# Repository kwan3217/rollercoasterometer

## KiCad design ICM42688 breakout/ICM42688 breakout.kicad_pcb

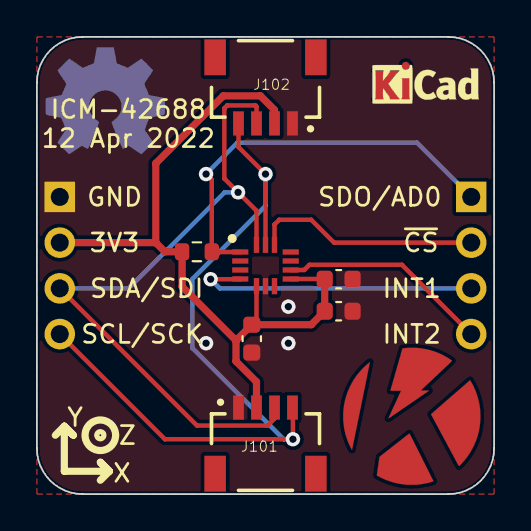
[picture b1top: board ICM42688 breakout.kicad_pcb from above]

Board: 2 copper layers, 25.4 x 25.4 mm, 10 parts (0 on the bottom side), 8 nets.

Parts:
C105: 10nF; C_0603_1608Metric
C106: 2.2uF; C_0603_1608Metric
C108: 100nF; C_0603_1608Metric
J101, J102: 1x04 1mm; JST04_1MM_RA
J103, J104: Conn_01x04; PinHeader_1x04_P2.54mm_Vertical
R101: 10k; R_0603_1608Metric
U102: ICM-42688; QFN50P300X250X97-14N
U501: MPU9250; Axis

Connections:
+3V3: C105.1, C106.1, C108.1, J101.2, J102.2, J103.2, R101.2, U102.5 (VDDIO), U102.8 (VDD)
/INT1: J104.3, U102.4 (INT1)
/INT2: J104.4, U102.9 (INT2)
/SCL/SCK: J101.4, J102.4, J103.4, U102.13 (SCL)
/SDA/SDI: J101.3, J102.3, J103.3, U102.14 (SDA)
/SDO/AD0: J104.1, R101.1, U102.1 (AD0)
/~CS: J104.2, U102.12 (~CS)
GND: C105.2, C106.2, C108.2, J101.1, J102.1, J103.1, U102.6 (GND)

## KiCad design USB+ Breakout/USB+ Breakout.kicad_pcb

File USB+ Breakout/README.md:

# USB+ breakout
This is for *USB+*, which is designed to be USB 2.0, *plus* other stuff on the other pairs, using a USB 3.0 cable.

This board is intended to test the concept, by having a pocket and remote USB receptacle, with a 1.5m USB 3.0 cable
to be plugged into both.

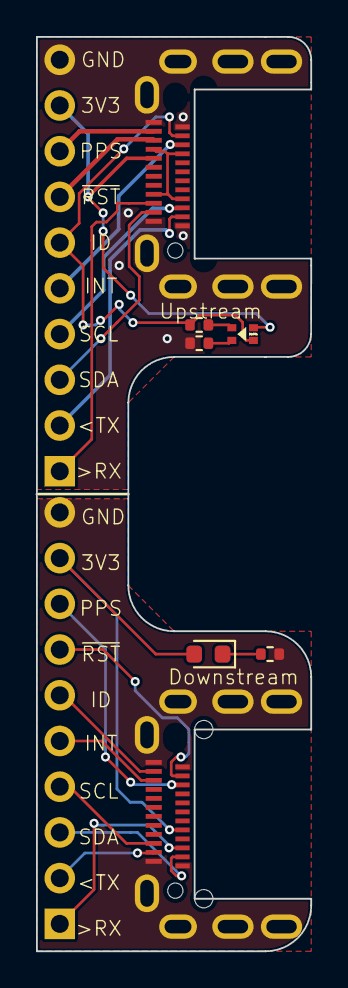
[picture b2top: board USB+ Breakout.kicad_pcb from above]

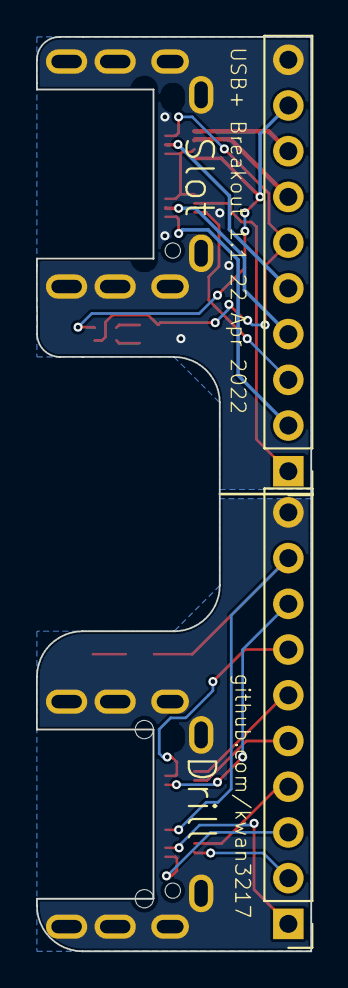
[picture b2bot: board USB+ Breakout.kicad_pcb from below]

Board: 2 copper layers, 15.2 x 50.8 mm, 9 parts (2 on the bottom side), 26 nets.

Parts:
D301: RED; LED_0603_1608Metric
D1601: GREEN, YELLOW; LEDKingbrightAPHB
J101, J301: Conn_01x10; PinHeader_1x10_P2.54mm_Vertical
J1601, J1602: USB_C_Receptacle; USB_C_Amphenol_MidMount
R301, R1602: 1.5k; R_0402_1005Metric
R1601: 330; R_0402_1005Metric

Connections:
/USB Cable/DG-: D1601.2 (K1), R1601.1
/USB Cable/DY-: D1601.4 (K2), R1602.1
/USB Cable/P_3V3: D1601.3 (A2), J101.9, J1601.A8 (SBU1)
/USB Cable/P_GND: J101.10, J1601.A1 (GND), J1601.A12 (GND), J1601.B1 (GND), J1601.B12 (GND), J1601.S1 (SHIELD), R1601.2
/USB Cable/P_ID: D1601.1 (A1), J101.6, J1601.B2 (TX2+), R1602.2
/USB Cable/P_INT: J101.5, J1601.B3 (TX2-)
/USB Cable/P_M~RST: J101.7, J1601.A10 (RX2-)
/USB Cable/P_PPS: J101.8, J1601.A11 (RX2+)
/USB Cable/P_RX_GPS: J101.1, J1601.A3 (TX1-)
/USB Cable/P_SCL: J101.4, J1601.B10 (RX1-)
/USB Cable/P_SDA: J101.3, J1601.A2 (TX1+)
/USB Cable/P_TX_GPS: J101.2, J1601.B11 (RX1+)
/USB Cable/Q_3V3: D301.2 (A), J301.9, J1602.B8 (SBU2)
/USB Cable/Q_D+: J1602.A6 (D+), J1602.B6 (D+)
/USB Cable/Q_D-: J1602.A7 (D-), J1602.B7 (D-)
/USB Cable/Q_GND: J301.10, J1602.A1 (GND), J1602.A12 (GND), J1602.B1 (GND), J1602.B12 (GND), J1602.S1 (SHIELD), R301.1
/USB Cable/Q_ID: J301.6, J1602.A11 (RX2+)
/USB Cable/Q_INT: J301.5, J1602.A10 (RX2-)
/USB Cable/Q_M~RST: J301.8, J1602.B3 (TX2-)
/USB Cable/Q_PPS: J301.7, J1602.B2 (TX2+)
/USB Cable/Q_RX_GPS: J301.1, J1602.B10 (RX1-)
/USB Cable/Q_SCL: J301.4, J1602.A3 (TX1-)
/USB Cable/Q_SDA: J301.3, J1602.B11 (RX1+)
/USB Cable/Q_TX_GPS: J301.2, J1602.A2 (TX1+)
/USB Cable/Q_VBUS: J1602.A4 (VBUS), J1602.A9 (VBUS), J1602.B4 (VBUS), J1602.B9 (VBUS)
unnamed: D301.1 (K), R301.2

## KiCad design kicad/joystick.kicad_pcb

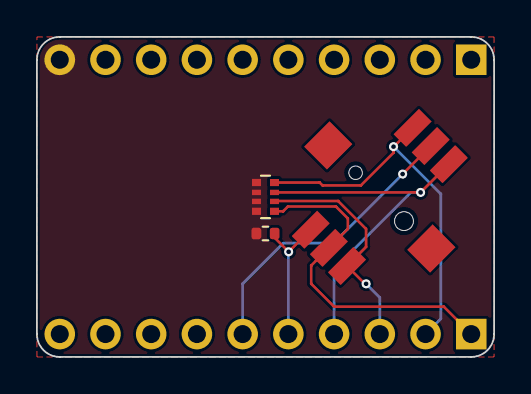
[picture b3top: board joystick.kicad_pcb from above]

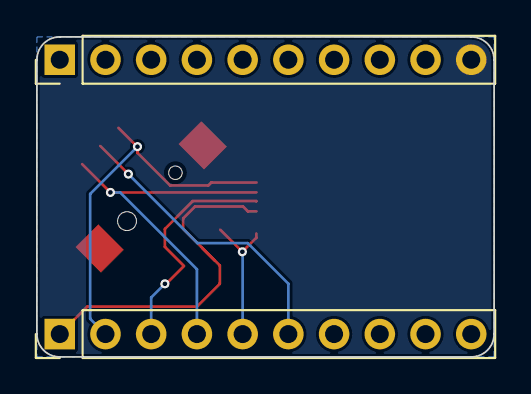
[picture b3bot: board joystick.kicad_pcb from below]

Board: 2 copper layers, 25.4 x 17.8 mm, 5 parts (2 on the bottom side), 7 nets.

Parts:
J3501, J3502: Conn_01x10; PinHeader_1x10_P2.54mm_Vertical
R3501: 2.2k; R_Array_Convex_4x0402
R3502: 5.1k; R_0402_1005Metric
S3501: JS1400

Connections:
/Joystick/Q_3V3: J3501.6, S3501.COM
/Joystick/Q_DOWN: J3501.3, R3501.6 (5), S3501.C
/Joystick/Q_GND: J3502.10, R3501.1 (4), R3501.2 (4), R3501.3 (4), R3501.4, R3502.1
/Joystick/Q_LEFT: J3501.5, R3502.2, S3501.A
/Joystick/Q_PUSH: J3501.1, R3501.5, S3501.PUSH
/Joystick/Q_RIGHT: J3501.4, R3501.7 (5), S3501.D
/Joystick/Q_UP: J3501.2, R3501.8 (5), S3501.B

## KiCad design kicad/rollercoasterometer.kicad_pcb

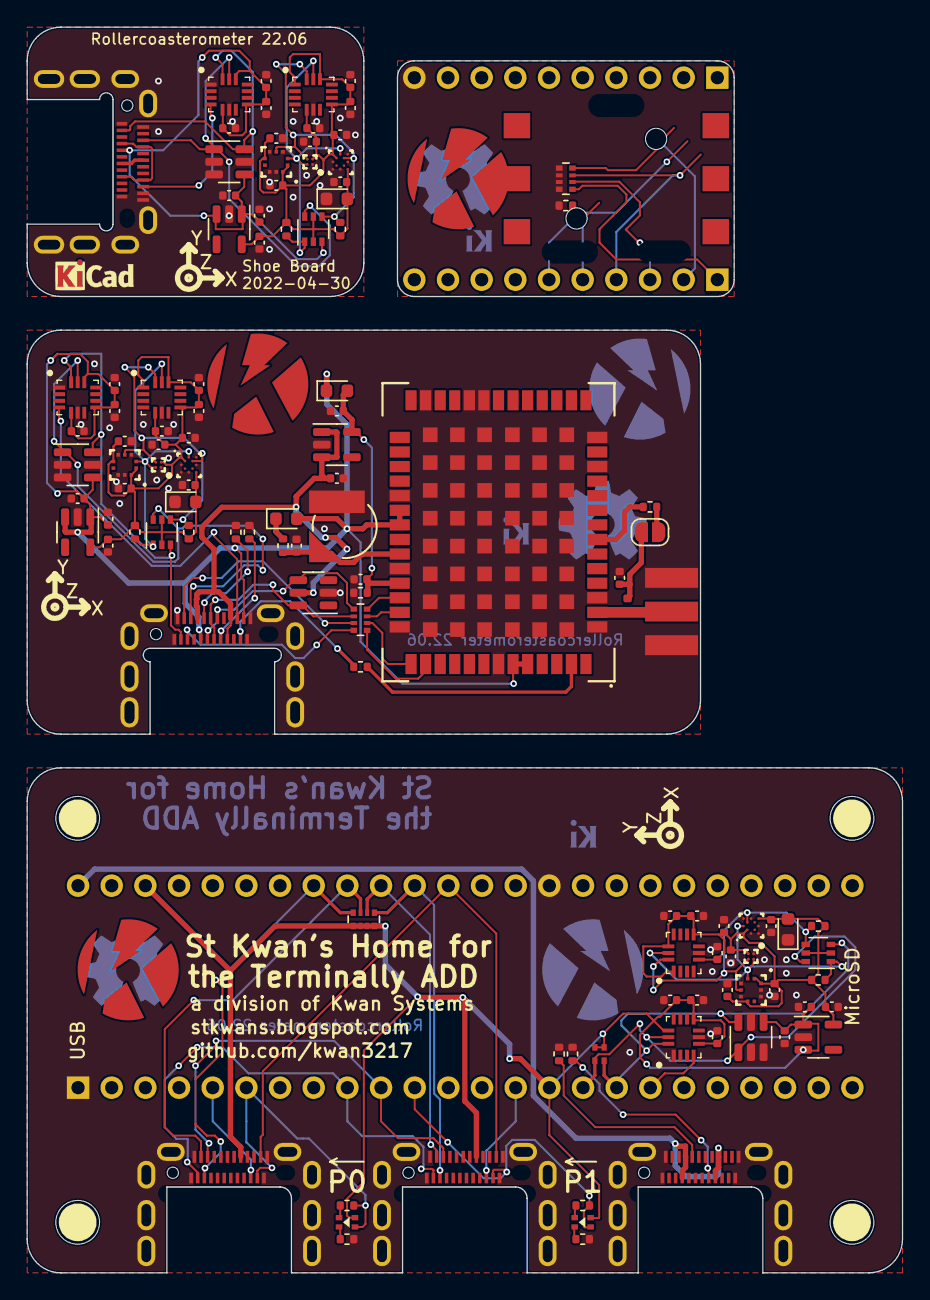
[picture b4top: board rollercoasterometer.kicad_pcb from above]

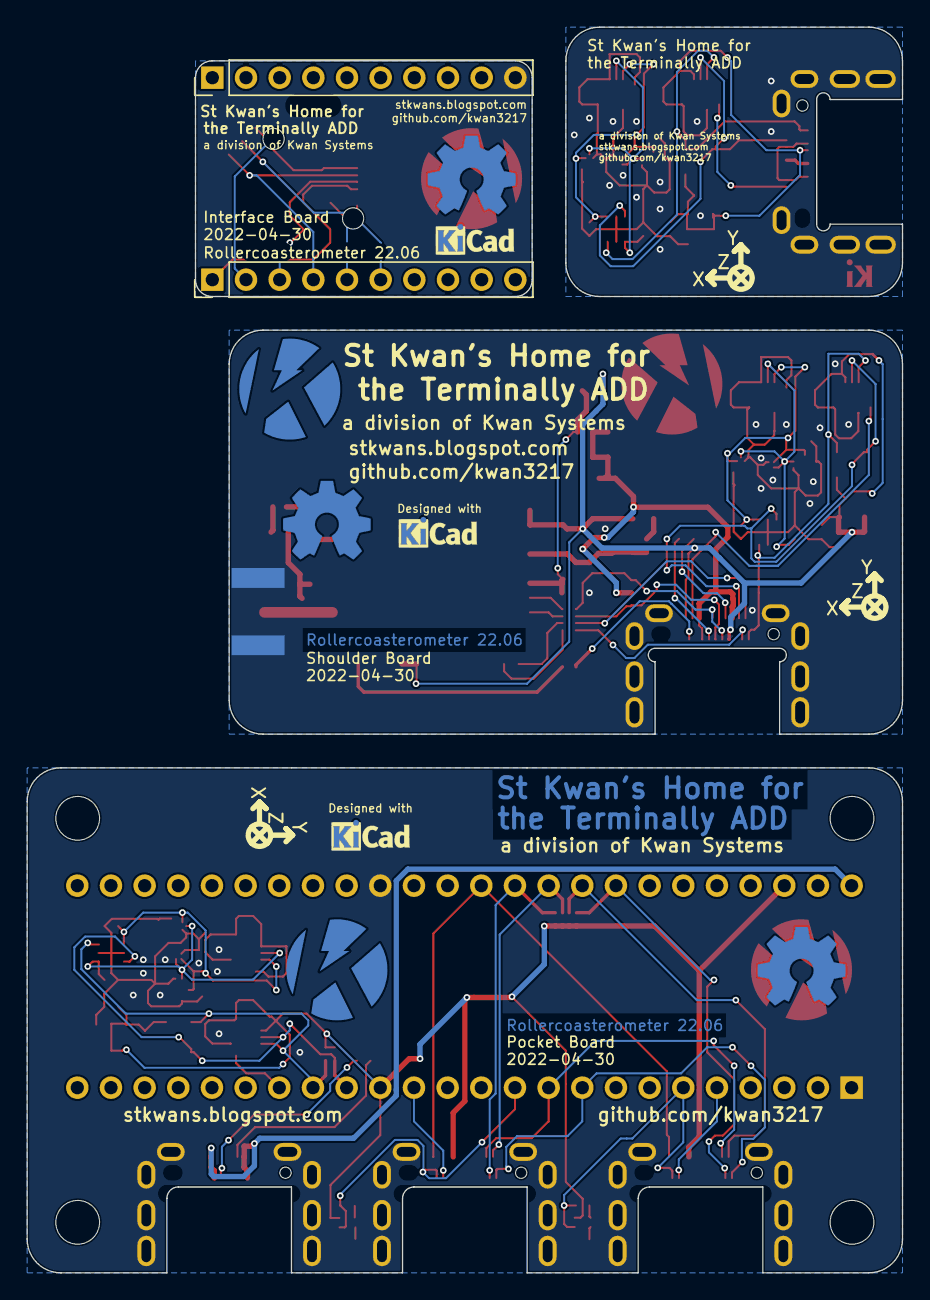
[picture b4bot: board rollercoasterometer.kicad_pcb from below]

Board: 2 copper layers, 66.0 x 94.0 mm, 136 parts (10 on the bottom side), 72 nets.

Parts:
B401: ML414H; Coin_Cell_ML414H
C205, C1205, C1305, C2105, C2705, C3205: 10nF; C_0402_1005Metric
C206, C1206, C1306, C2106, C2706, C3206: 2.2uF; C_0402_1005Metric
C208, C611, C704, C901, C910, C1122, C1155, C1208, C1308, C1804, C2108, C2322, C2355, C2411, C2501, C2510, C2708, C2804, C2901, C2910, C3208, C3322, C3355, C3411: 100nF; C_0402_1005Metric
C401: 47pF; C_0402_1005Metric
C436, C438, C501, C505, C1001, C1005, C1901, C1905, C3001, C3005: 1uF; C_0402_1005Metric
D338, D401: 0.5A/420mV; D_0603_1608Metric
D1001, D1905, D3001: RED; LED_0603_1608Metric
D1401, D1601: GREEN, YELLOW; LEDKingbrightAPHB
G101, G102, G301, G302, G3502: KwanSystems; StKwansSoldermask
G103, G303, G1501, G3503: DesignedWithKicad; Symbol_KiCAD-Logo_CopperAndSilkScreenTop_small
G104, G304, G3504: OSHW; OSHW-Symbol_6.7x6mm_SolderMask
G105, G305, G1505: Axis
J101, J1401, J1402, J1601, J1602: USB_C_Receptacle; USB_C_Amphenol_MidMount
J120, J125, J127, J129: STANDOFF; STANDOFF_NONPLATED
J401: SMA; SMA-EDGE
J402: NormallyClosed; SolderJumper-2_P1.3mm_MaskBridged_RoundedPad1.0x1.5mm
J3501, J3502: Conn_01x10; PinHeader_1x10_P2.54mm_Vertical
L401: Ferrite 120NH; L_0402_1005Metric
Q801, Q2001, Q3101: NMOS; SOT-363_SC-70-6
R101, R102, R301, R302, R436, R801, R802, R2001, R2002, R3101, R3102, R3502: 5.1k; R_0402_1005Metric
R116: 2.2k; R_Array_Convex_2x0402
R138, R3501: 2.2k; R_Array_Convex_4x0402
R407, R453: 27; R_0402_1005Metric
R438: 100k; R_0402_1005Metric
R439: 27; R_Array_Convex_4x0402
R1401, R1601: 330; R_0402_1005Metric
R1402, R1602: 1.5k; R_0402_1005Metric
S3501: JS5208
U104: Teensy4.1; Teensy2x24
U201, U1201, U1301, U2101, U2701, U3201: ICM-42688; QFN50P300X250X97-14N
U301: USBLC6-4SC6; SOT-23-6
U401: ZED_F9R; ZED-F9x
U501: TCR2EF 3.3V; SOT-23-5
U601, U2401, U3401: AK09918; AK09918C
U704, U1801, U2801: TLE493D-W2B6; SOT-23-6
U901, U2501, U2901: BMP384
U1001, U1901, U3001: TCR2EF 1.8V; SOT-23-5
U1101, U2201, U3301: BMM150

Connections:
+3V3: C2705.1, C2706.1, C2708.1, C2804.1, C3001.1, D1401.3 (A2), D1601.3 (A2), J1401.A8 (SBU1), J1601.A8 (SBU1), R116.3, R116.4 (3), R138.5, R138.6 (5), R138.7 (5), R138.8 (5), U104.15 (+3V3), U104.46 (+3V3), U2701.5 (VDDIO), U2701.8 (VDD), U2701.12 (~CS), U2801.4 (VDD), U3001.1 (IN), U3001.3 (EN)
+5V: J101.A4 (VBUS), J101.A9 (VBUS), J101.B4 (VBUS), J101.B9 (VBUS), U104.48 (Vin)
/CC1: J101.A5 (CC1), R101.2
/CC2: J101.B5 (CC2), R102.2
/Joystick/Q_3V3: J3501.6, S3501.COM
/Joystick/Q_DOWN: J3501.3, R3501.6 (5), S3501.C
/Joystick/Q_GND: J3502.10, R3501.1 (4), R3501.2 (4), R3501.3 (4), R3501.4, R3502.1
/Joystick/Q_LEFT: J3501.5, R3502.2, S3501.A
/Joystick/Q_PUSH: J3501.1, R3501.5, S3501.PUSH
/Joystick/Q_RIGHT: J3501.4, R3501.7 (5), S3501.D
/Joystick/Q_UP: J3501.2, R3501.8 (5), S3501.B
/P0_ID: D1401.1 (A1), J1401.B2 (TX2+), R1402.2, U104.6 (D4~)
/P0_INT: J1401.B3 (TX2-), U104.5 (D3~)
/P0_SCL: J1401.B10 (RX1-), R138.4, U104.41 (~D19)
/P0_SDA: J1401.A2 (TX1+), R138.3 (4), U104.40 (~D18)
/P1_ID: D1601.1 (A1), J1601.B2 (TX2+), R1602.2, U104.11 (D9~)
/P1_INT: J1601.B3 (TX2-), U104.14 (D12~)
/P1_SCL: J1601.B10 (RX1-), R138.1 (4), U104.38 (D16)
/P1_SDA: J1601.A2 (TX1+), R138.2 (4), U104.39 (D17)
/P2_INT: U104.18 (D26), U2701.4 (INT1)
/P2_SCL: Q3101.6 (D), R116.1 (4), U104.16 (D24~), U2701.13 (SCL), U2801.1 (SCL/INT)
/P2_SDA: Q3101.3 (D), R116.2 (4), U104.17 (D25~), U2701.14 (SDA), U2801.6 (SDA)
/PPS: J1401.A11 (RX2+), J1601.A11 (RX2+), U104.37 (~D15)
/Pocket Sensor Block/Q_1V8: C2901.1, C2910.1, C3005.1, C3205.1, C3206.1, C3208.1, C3322.1, C3355.1, C3411.1, D3001.2 (A), Q3101.2 (G), Q3101.5 (G), R3101.2, R3102.2, U2901.1 (VDDIO), U2901.6 (CSB), U2901.10 (VDD), U3001.5 (OUT), U3201.1 (AD0), U3201.5 (VDDIO), U3201.8 (VDD), U3201.12 (~CS), U3301.A1 (PS), U3301.B2 (VDDIO), U3301.E5 (VDD), U3401.B1 (VDD)
/Pocket Sensor Block/SCL_1V8: Q3101.1 (S), R3102.1, U2901.2 (SCK), U3201.13 (SCL), U3301.A3 (SCK), U3401.A2 (SCL)
/Pocket Sensor Block/SDA_1V8: Q3101.4 (S), R3101.1, U2901.4 (SDI), U3201.14 (SDA), U3301.B4 (SDI), U3401.B2 (SDA)
/RX_GPS: J1401.A3 (TX1-), J1601.A3 (TX1-), U104.10 (D8~)
/Shoe/Q_3V3: C205.1, C206.1, C208.1, C1804.1, C1901.1, J1402.B8 (SBU2), U201.5 (VDDIO), U201.8 (VDD), U201.12 (~CS), U1801.4 (VDD), U1901.1 (IN), U1901.3 (EN)
/Shoe/Q_GND: C205.2, C206.2, C208.2, C1804.2, C1901.2, C1905.2, C2105.2, C2106.2, C2108.2, C2322.2, C2355.2, C2411.2, C2501.2, C2510.2, D1905.1 (K), J1402.A1 (GND), J1402.A11 (RX2+), J1402.A12 (GND), J1402.B1 (GND), J1402.B12 (GND), J1402.S1 (SHIELD), U201.1 (AD0), U201.6 (GND), U1801.2 (GND), U1801.3 (GND), U1801.5 (GND), U1901.2 (GND), U2101.6 (GND), U2201.A5 (CSB), U2201.C1 (SDO), U2201.C5 (GND), U2201.E1 (GND), U2201.E3 (GND), U2401.A1 (VSS), U2501.3 (VSS), U2501.5 (SDO), U2501.8 (VSS), U2501.9 (VSS)
/Shoe/Q_INT: J1402.A10 (RX2-), U201.4 (INT1)
/Shoe/Q_SCL: J1402.A3 (TX1-), Q2001.6 (D), U201.13 (SCL), U1801.1 (SCL/INT)
/Shoe/Q_SDA: J1402.B11 (RX1+), Q2001.3 (D), U201.14 (SDA), U1801.6 (SDA)
/Shoe/Sensor Block/Q_1V8: C1905.1, C2105.1, C2106.1, C2108.1, C2322.1, C2355.1, C2411.1, C2501.1, C2510.1, D1905.2 (A), Q2001.2 (G), Q2001.5 (G), R2001.2, R2002.2, U1901.5 (OUT), U2101.1 (AD0), U2101.5 (VDDIO), U2101.8 (VDD), U2101.12 (~CS), U2201.A1 (PS), U2201.B2 (VDDIO), U2201.E5 (VDD), U2401.B1 (VDD), U2501.1 (VDDIO), U2501.6 (CSB), U2501.10 (VDD)
/Shoe/Sensor Block/SCL_1V8: Q2001.1 (S), R2002.1, U2101.13 (SCL), U2201.A3 (SCK), U2401.A2 (SCL), U2501.2 (SCK)
/Shoe/Sensor Block/SDA_1V8: Q2001.4 (S), R2001.1, U2101.14 (SDA), U2201.B4 (SDI), U2401.B2 (SDA), U2501.4 (SDI)
/Shoe/USB+ cable/DG-: D1401.2 (K1), R1401.1
/Shoe/USB+ cable/DY-: D1401.4 (K2), R1402.1
/Shoe/USB+ cable/Q_D+: J1402.A6 (D+), J1402.B6 (D+)
/Shoe/USB+ cable/Q_D-: J1402.A7 (D-), J1402.B7 (D-)
/Shoe/USB+ cable/Q_VBUS: J1402.A4 (VBUS), J1402.A9 (VBUS), J1402.B4 (VBUS), J1402.B9 (VBUS)
/Shoulder/GPS Rover/DM-: R439.8 (5), U401.39 (USB_D-)
/Shoulder/GPS Rover/DP-: R439.7 (5), U401.40 (USB_D+)
/Shoulder/GPS Rover/RF_IN: J401.1 (In), L401.1, U401.2 (RF_IN)
/Shoulder/GPS Rover/RX/MOSI-: R439.5, U401.43 (RX/MOSI)
/Shoulder/GPS Rover/TIMEPULSE-: R453.1, U401.53 (TIMEPULSE)
/Shoulder/GPS Rover/TX/MISO-: R439.6 (5), U401.42 (TX/MISO)
/Shoulder/GPS Rover/VBAT+: D401.1 (K), R436.1
/Shoulder/GPS Rover/V_BATT: B401.1 (+), C436.1, R436.2, U401.36 (V_BKCP)
/Shoulder/GPS Rover/V_RF: R407.2, U401.7 (VCC_RF)
/Shoulder/GPS Rover/V_RF-: J402.2 (B), R407.1
/Shoulder/GPS Rover/V_RF--: C401.1, J402.1 (A), L401.2
/Shoulder/Q_3V3: C704.1, C1001.1, C1305.1, C1306.1, C1308.1, D338.1 (K), D401.2 (A), J1602.A11 (RX2+), J1602.B8 (SBU2), U401.33 (VCC), U401.34 (VCC), U401.49 (~RESET), U401.50 (~SAFEBOOT), U704.4 (VDD), U1001.1 (IN), U1001.3 (EN), U1301.5 (VDDIO), U1301.8 (VDD), U1301.12 (~CS)
/Shoulder/Q_CC1: J1602.A5 (CC1), R301.1
/Shoulder/Q_CC2: J1602.B5 (CC2), R302.1
/Shoulder/Q_D+: J1602.A6 (D+), J1602.B6 (D+), R439.2 (4), U301.6 (IO4)
/Shoulder/Q_D-: J1602.A7 (D-), J1602.B7 (D-), R439.1 (4), U301.4 (IO3)
/Shoulder/Q_GND: B401.2 (-), C401.2, C436.2, C438.2, C501.2, C505.2, C611.2, C704.2, C901.2, C910.2, C1001.2, C1005.2, C1122.2, C1155.2, C1205.2, C1206.2, C1208.2, C1305.2, C1306.2, C1308.2, D1001.1 (K), J401.2 (Ext), J1602.A1 (GND), J1602.A12 (GND), J1602.B1 (GND), J1602.B12 (GND), J1602.S1 (SHIELD), R301.2, R302.2, R438.1, U301.2 (VN), U401.1 (GND), U401.3 (GND), U401.12 (GND), U401.14 (GND), U401.22 (WT), U401.23 (DIR), U401.26 (RX2), U401.32 (GND), U401.37 (GND), U401.41 (GND), U401.48 (GND), U401.PAD (GND), U501.2 (GND), U601.A1 (VSS), U704.2 (GND), U704.3 (GND), U704.5 (GND), U901.3 (VSS), U901.5 (SDO), U901.8 (VSS), U901.9 (VSS), U1001.2 (GND), U1101.A5 (CSB), U1101.C1 (SDO), U1101.C5 (GND), U1101.E1 (GND), U1101.E3 (GND), U1201.6 (GND), U1301.1 (AD0), U1301.6 (GND)
/Shoulder/Q_INT: J1602.A10 (RX2-), U1301.4 (INT1)
/Shoulder/Q_PPS: J1602.B2 (TX2+), R453.2
/Shoulder/Q_RX_GPS: J1602.B10 (RX1-), R439.4
/Shoulder/Q_SCL: J1602.A3 (TX1-), Q801.6 (D), U704.1 (SCL/INT), U1301.13 (SCL)
/Shoulder/Q_SDA: J1602.B11 (RX1+), Q801.3 (D), U704.6 (SDA), U1301.14 (SDA)
/Shoulder/Q_TX_GPS: J1602.A2 (TX1+), R439.3 (4)
/Shoulder/Q_VBUS: C501.1, J1602.A4 (VBUS), J1602.A9 (VBUS), J1602.B4 (VBUS), J1602.B9 (VBUS), U301.5 (VP), U501.1 (IN), U501.3 (EN)
/Shoulder/Sensor Block/Q_1V8: C611.1, C901.1, C910.1, C1005.1, C1122.1, C1155.1, C1205.1, C1206.1, C1208.1, D1001.2 (A), Q801.2 (G), Q801.5 (G), R801.2, R802.2, U601.B1 (VDD), U901.1 (VDDIO), U901.6 (CSB), U901.10 (VDD), U1001.5 (OUT), U1101.A1 (PS), U1101.B2 (VDDIO), U1101.E5 (VDD), U1201.1 (AD0), U1201.5 (VDDIO), U1201.8 (VDD), U1201.12 (~CS)
/Shoulder/Sensor Block/SCL_1V8: Q801.1 (S), R802.1, U601.A2 (SCL), U901.2 (SCK), U1101.A3 (SCK), U1201.13 (SCL)
/Shoulder/Sensor Block/SDA_1V8: Q801.4 (S), R801.1, U601.B2 (SDA), U901.4 (SDI), U1101.B4 (SDI), U1201.14 (SDA)
/Shoulder/USB+ cable/DG-: D1601.2 (K1), R1601.1
/Shoulder/USB+ cable/DY-: D1601.4 (K2), R1602.1
/Shoulder/V_USBDETECT: C438.1, C505.1, D338.2 (A), R438.2, U401.38 (V_USB), U501.5 (OUT)
/TX_GPS: J1401.B11 (RX1+), J1601.B11 (RX1+), U104.9 (D7~)
GND: C2705.2, C2706.2, C2708.2, C2804.2, C2901.2, C2910.2, C3001.2, C3005.2, C3205.2, C3206.2, C3208.2, C3322.2, C3355.2, C3411.2, D3001.1 (K), J101.A1 (GND), J101.A12 (GND), J101.B1 (GND), J101.B12 (GND), J101.S1 (SHIELD), J1401.A1 (GND), J1401.A12 (GND), J1401.B1 (GND), J1401.B12 (GND), J1401.S1 (SHIELD), J1601.A1 (GND), J1601.A12 (GND), J1601.B1 (GND), J1601.B12 (GND), J1601.S1 (SHIELD), R101.1, R102.1, R1401.2, R1601.2, U104.1 (GND), U104.34 (GND), U2701.1 (AD0), U2701.6 (GND), U2801.2 (GND), U2801.3 (GND), U2801.5 (GND), U2901.3 (VSS), U2901.5 (SDO), U2901.8 (VSS), U2901.9 (VSS), U3001.2 (GND), U3201.6 (GND), U3301.A5 (CSB), U3301.C1 (SDO), U3301.C5 (GND), U3301.E1 (GND), U3301.E3 (GND), U3401.A1 (VSS)

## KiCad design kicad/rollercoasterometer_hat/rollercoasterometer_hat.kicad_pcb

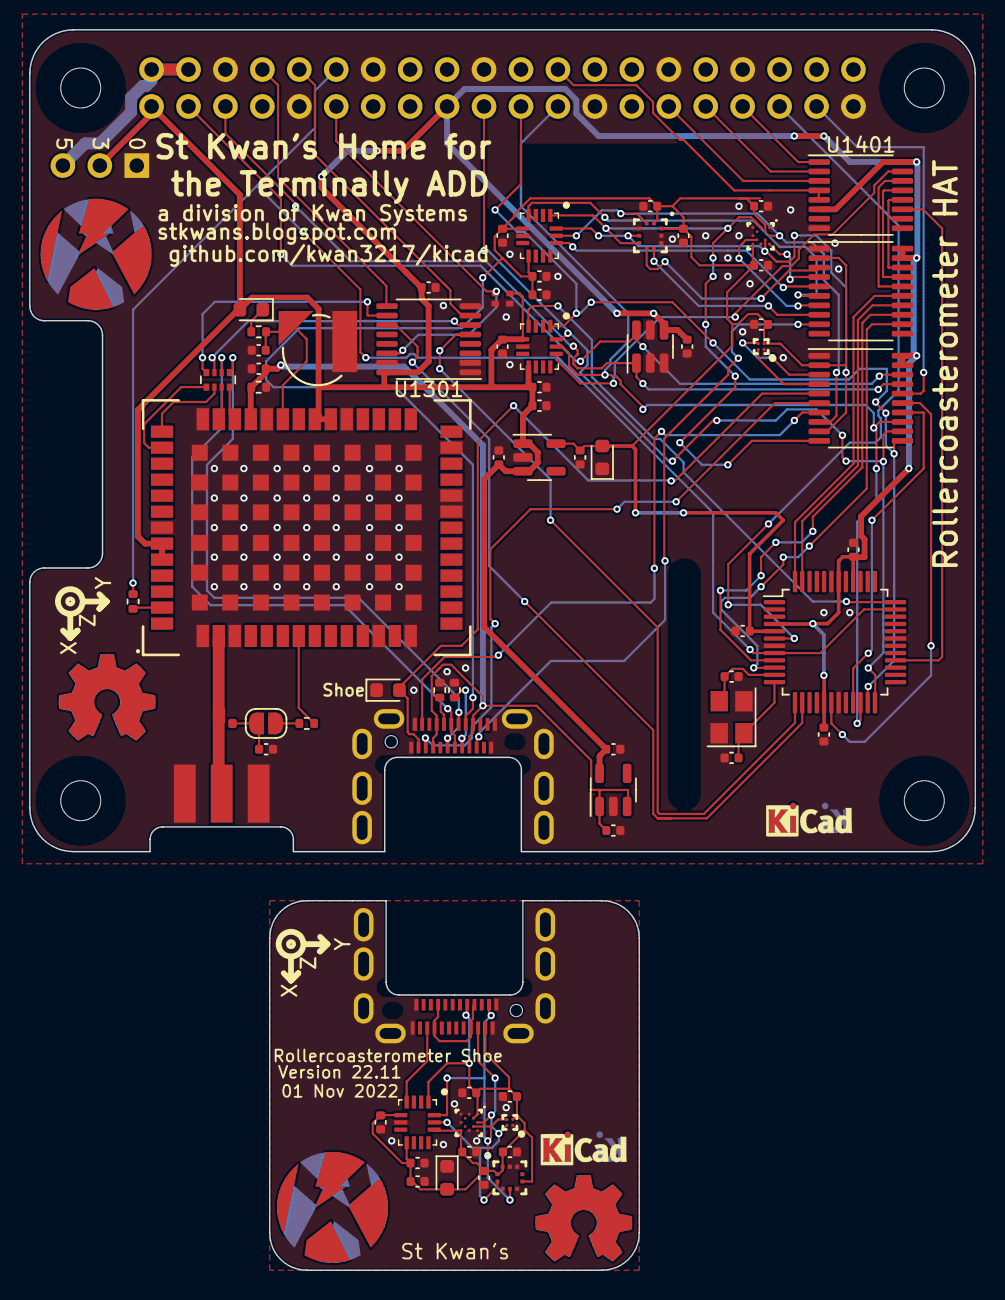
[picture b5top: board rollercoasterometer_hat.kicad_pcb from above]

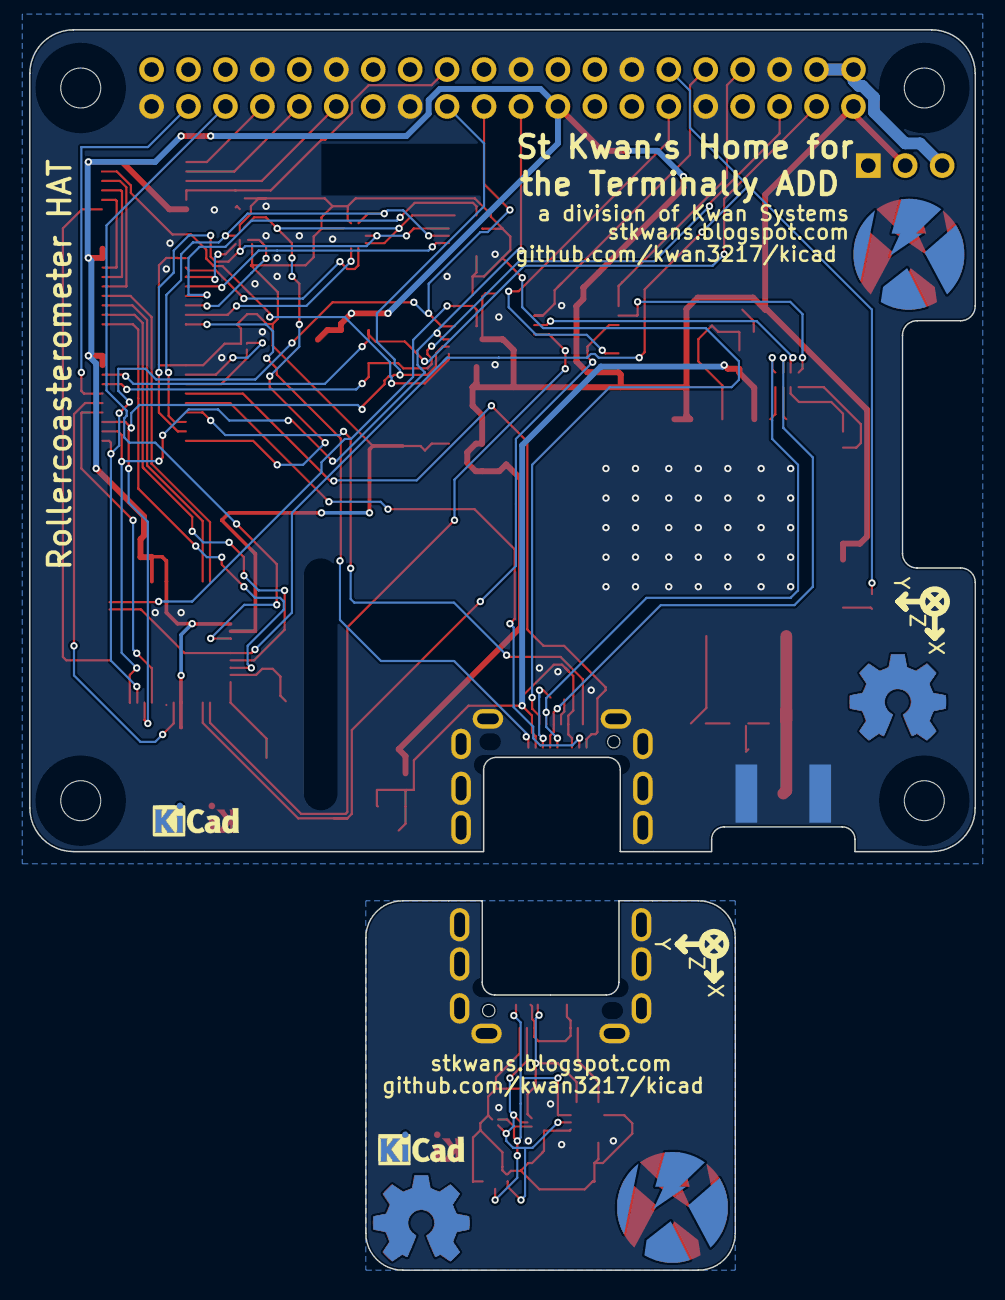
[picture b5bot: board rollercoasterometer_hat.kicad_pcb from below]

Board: 2 copper layers, 65.0 x 56.5 mm, 86 parts (6 on the bottom side), 73 nets.

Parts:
B201: ML414H; Coin_Cell_ML414H
C201: 47pF; C_0402_1005Metric
C236, C238, C401, C405, C501, C505: 1uF; C_0402_1005Metric
C605, C805, C1605: 10nF; C_0402_1005Metric
C606, C806, C1606: 2.2uF; C_0402_1005Metric
C608, C704, C808, C922, C955, C1011, C1101, C1110, C1205, C1217, C1240, C1301, C1608, C1722, C1755, C1811, C1901, C1910: 100nF; C_0402_1005Metric
C1211, C1212: 22pF; C_0402_1005Metric
D201: 0.5A/420mV; D_0603_1608Metric
D301, D302, D501: RED; LED_0603_1608Metric
G101, G1501: Axis
G102, G105, G1502, G1505: KwanSystems; StKwansSoldermask
G103, G107, G1503, G1507: DesignedWithKicad; Symbol_KiCAD-Logo_CopperAndSilkScreenTop_small
G104, G106, G1504, G1506: OSHW; OSHW-Symbol_6.7x6mm_SolderMask
J101: Raspberry_Pi_40; PiHAT
J102: Conn_01x03; PinHeader_1x03_P2.54mm_Horizontal
J201: SMA; SMA-EDGE
J202: NormallyClosed; SolderJumper-2_P1.3mm_MaskBridged_RoundedPad1.0x1.5mm
J301, J302: USB_C_Receptacle; USB_C_Amphenol_MidMount_with_cutout
L201: Ferrite 120NH; L_0402_1005Metric
R238: 100k; R_0402_1005Metric
R239: 27; R_Array_Convex_4x0402
R253, R407: 27; R_0402_1005Metric
R301, R302, R436: 5.1k; R_0402_1005Metric
R1301: 10k; R_Array_Convex_2x0402
U201: ZED_F9R; ZED-F9x
U401: TCR2EF 3.3V; SOT-23-5
U501: TCR2EF 1.8V; SOT-23-5
U601, U801, U1601: ICM-42688; QFN50P300X250X97-14N
U701: TLE493D-W2B6; SOT-23-6
U901, U1701: BMM150
U1001, U1801: AK09918; AK09918C
U1101, U1901: BMP384
U1201: LPC2103; LQFP-48_7x7mm_P0.5mm
U1301: 743253; TSSOP-16_4.4x5mm_P0.65mm
U1401: 74LS138; TSSOP-16_4.4x5mm_P0.65mm
U1402, U1403: TXS0108; TSSOP-20_4.4x6.5mm_P0.65mm
Y1201: 12MHz; Crystal_SMD_Abracon_ABM8G-4Pin_3.2x2.5mm

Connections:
+1V8: C505.1, C805.1, C806.1, C808.1, C922.1, C955.1, C1011.1, C1101.1, C1110.1, C1205.1, D501.2 (A), J301.A8 (SBU1), U501.5 (OUT), U801.5 (VDDIO), U801.8 (VDD), U901.B2 (VDDIO), U901.E5 (VDD), U1001.B1 (VDD), U1101.1 (VDDIO), U1101.10 (VDD), U1201.5 (VDD(1V8)), U1402.2 (VLO), U1403.2 (VLO)
+3V3: C405.1, C501.1, C605.1, C606.1, C608.1, C704.1, C1217.1, C1240.1, C1301.1, D201.2 (A), J101.1 (3V3), J101.17 (3V3), J102.2, R1301.4 (3), U201.33 (VCC), U201.34 (VCC), U201.49 (~RESET), U201.50 (~SAFEBOOT), U401.5 (OUT), U501.1 (IN), U501.3 (EN), U601.5 (VDDIO), U601.8 (VDD), U701.4 (VDD), U1201.4 (VBAT), U1201.17 (VDD(3V3)), U1201.40 (VDD(3V3)), U1201.42 (VDDA), U1301.16 (VCC), U1401.6 (E3), U1401.16 (VCC), U1402.19 (VHI), U1402.20 (EN), U1403.19 (VHI), U1403.20 (EN)
+5V: J101.2 (5V), J101.4 (5V), J102.3
/Bus Level Converter/~CS_6D18_3V3: U1401.14 (O1), U1402.16 (B3)
/Bus Level Converter/~CS_BMM_3V3: U1401.13 (O2), U1402.17 (B2)
/Bus Level Converter/~CS_BMP_3V3: U1401.12 (O3), U1402.18 (B1)
/CS0: J101.33 ((PWM1)_GPIO13), U1401.1 (A0)
/CS1: J101.31 (GPIO6), U1401.2 (A1)
/CS2: J101.29 (GPIO5), U1401.3 (A2)
/D+: J301.A6 (D+), J301.B6 (D+), R239.2 (4)
/D-: J301.A7 (D-), J301.B7 (D-), R239.1 (4)
/DRDY_6D18_1V8: U801.4 (INT1), U1402.6 (A4)
/DRDY_6D18_3V3: U1201.48 ((CAP1.3/SDA1)P0.18), U1402.15 (B4)
/DRDY_6D33_3V3: U601.4 (INT1), U1201.36 ((CTS1/CAP1.1/AD0.4)P0.11)
/DRDY_BMM_1V8: U901.D4 (DRDY), U1402.7 (A5)
/DRDY_BMM_3V3: U1201.47 ((CAP1.2/SCL1)P0.17), U1402.14 (B5)
/DRDY_BMP_1V8: U1101.7 (INT), U1402.8 (A6)
/DRDY_BMP_3V3: U1201.9 ((TMS/CAP2.1)P0.28), U1402.13 (B6)
/GPS/DM-: R239.8 (5), U201.39 (USB_D-)
/GPS/DP-: R239.7 (5), U201.40 (USB_D+)
/GPS/RF_IN: J201.1 (In), L201.1, U201.2 (RF_IN)
/GPS/RX/MOSI-: R239.5, U201.43 (RX/MOSI)
/GPS/TIMEPULSE-: R253.1, U201.53 (TIMEPULSE)
/GPS/TX/MISO-: R239.6 (5), U201.42 (TX/MISO)
/GPS/VBAT+: D201.1 (K), R436.1
/GPS/V_BATT: B201.1 (+), C236.1, R436.2, U201.36 (V_BKCP)
/GPS/V_RF: R407.2, U201.7 (VCC_RF)
/GPS/V_RF-: J202.2 (B), R407.1
/GPS/V_RF--: C201.1, J202.1 (A), L201.2
/GPS_RX: R239.4, U1301.10 (2B1)
/GPS_TX: R239.3 (4), U1301.6 (1B1)
/LPC_RX: U1201.14 ((RXD0/MAT3.2)P0.1), U1301.11 (2B2)
/LPC_TX: U1201.13 ((TXD0/MAT3.1)P0.0), U1301.5 (1B2)
/LPC_~RESET: J101.35 ((MISO)_GPIO19), U1201.6 (~RST)
/MISO_1V8: U801.1 (AD0), U901.C1 (SDO), U1101.5 (SDO), U1403.10 (A8)
/MISO_3V3: J101.21 ((SPI_MISO)_GPIO9), U601.1 (AD0), U1201.23 ((MISO0/MAT0.1)P0.5), U1403.11 (B8)
/MOSI_1V8: U801.14 (SDA), U901.B4 (SDI), U1101.4 (SDI), U1403.9 (A7)
/MOSI_3V3: J101.19 ((SPI_MOSI)_GPIO10), U601.14 (SDA), U1201.24 ((MOSI0/CAP0.2)P0.6), U1403.12 (B7)
/PPS: J101.12 (GPIO18_(GEN1)), R253.2, U1201.8 ((~TRST/CAP2.0)P0.27), U1201.35 ((RTS1/CAP1.0/AD0.3)P0.10)
/P_RET_1V8: D301.2 (A), J301.B11 (RX1+), U1403.5 (A3)
/P_RET_3V3: J101.37 (GPIO26), U1403.16 (B3)
/Q_1V8: C1605.1, C1606.1, C1608.1, C1722.1, C1755.1, C1811.1, C1901.1, C1910.1, D302.2 (A), J302.A2 (TX1+), J302.B8 (SBU2), U1601.1 (AD0), U1601.5 (VDDIO), U1601.8 (VDD), U1601.12 (~CS), U1701.A1 (PS), U1701.B2 (VDDIO), U1701.E5 (VDD), U1801.B1 (VDD), U1901.1 (VDDIO), U1901.6 (CSB), U1901.10 (VDD)
/Q_GND: C1605.2, C1606.2, C1608.2, C1722.2, C1755.2, C1811.2, C1901.2, C1910.2, D302.1 (K), J302.A1 (GND), J302.A12 (GND), J302.B1 (GND), J302.B12 (GND), J302.S1 (SHIELD), U1601.6 (GND), U1701.A5 (CSB), U1701.C1 (SDO), U1701.C5 (GND), U1701.E1 (GND), U1701.E3 (GND), U1801.A1 (VSS), U1901.3 (VSS), U1901.5 (SDO), U1901.8 (VSS), U1901.9 (VSS)
/Q_SCL_1V8: J302.A3 (TX1-), U1601.13 (SCL), U1701.A3 (SCK), U1801.A2 (SCL), U1901.2 (SCK)
/Q_SDA_1V8: J302.B11 (RX1+), U1601.14 (SDA), U1701.B4 (SDI), U1801.B2 (SDA), U1901.4 (SDI)
/Q_SHOE_INT: J302.A10 (RX2-), U1601.4 (INT1)
/RX_PI: J101.10 ((RXD0)_GPIO15), U1301.7 (1A)
/SCK_1V8: U801.13 (SCL), U901.A3 (SCK), U1101.2 (SCK), U1403.8 (A6)
/SCK_3V3: J101.23 ((SPI_SCLK)_GPIO11), U601.13 (SCL), U1201.22 ((SCK0/CAP0.1)P0.4), U1403.13 (B6)
/SCL_LPC_1V8: J301.B10 (RX1-), U1403.6 (A4)
/SCL_LPC_3V3: U1201.18 ((SCL0/CAP0.0)P0.2), U1403.15 (B4)
/SCL_PI_1V8: U1001.A2 (SCL), U1403.4 (A2)
/SCL_PI_3V3: J101.5 ((SCL1)_GPIO3), U701.1 (SCL/INT), U1403.17 (B2)
/SDA_LPC_1V8: J301.A2 (TX1+), U1403.7 (A5)
/SDA_LPC_3V3: U1201.21 ((SDA0/MAT0.0)P0.3), U1403.14 (B5)
/SDA_PI_1V8: U1001.B2 (SDA), U1403.3 (A1)
/SDA_PI_3V3: J101.3 ((SDA1)_GPIO2), U701.6 (SDA), U1403.18 (B1)
/SHOE_INT_1V8: J301.B3 (TX2-), U1402.9 (A7)
/SHOE_INT_3V3: U1201.10 ((TCK/CAP2.2)P0.29), U1402.12 (B7)
/TX_PI: J101.8 ((TXD0)_GPIO14), U1301.9 (2A)
/Timer/XTAL1: C1211.2, U1201.11 (XTAL1), Y1201.3
/Timer/XTAL2: C1212.2, U1201.12 (XTAL2), Y1201.1
/UART_S0: J101.11 (GPIO17_(GEN0)), R1301.1 (4), U1301.14 (S0)
/USB+ Cable/P_CC1: J301.A5 (CC1), R302.2
/USB+ Cable/P_CC2: J301.B5 (CC2), R301.2
/VBUS: C238.1, C401.1, J301.A4 (VBUS), J301.A9 (VBUS), J301.B4 (VBUS), J301.B9 (VBUS), R238.2, U201.38 (V_USB), U401.1 (IN), U401.3 (EN)
/~CE0: J101.24 ((~SPI_CE0)_GPIO8), U1401.4 (E1), U1401.5 (E2)
/~CS_6D18_1V8: U801.12 (~CS), U1402.5 (A3)
/~CS_6D33: U601.12 (~CS), U1401.15 (O0)
/~CS_BMM_1V8: U901.A5 (CSB), U1402.4 (A2)
/~CS_BMP_1V8: U1101.6 (CSB), U1402.3 (A1)
/~CS_LPC_3V3: U1201.28 ((SSEL0/MAT2.0)P0.7), U1401.11 (O4)
GND: B201.2 (-), C201.2, C236.2, C238.2, C401.2, C405.2, C501.2, C505.2, C605.2, C606.2, C608.2, C704.2, C805.2, C806.2, C808.2, C922.2, C955.2, C1011.2, C1101.2, C1110.2, C1205.2, C1211.1, C1212.1, C1217.2, C1240.2, C1301.2, D301.1 (K), D501.1 (K), J101.6 (GND), J101.9 (GND), J101.14 (GND), J101.20 (GND), J101.25 (GND), J101.30 (GND), J101.34 (GND), J101.39 (GND), J102.1, J201.2 (Ext), J301.A1 (GND), J301.A12 (GND), J301.B1 (GND), J301.B12 (GND), J301.S1 (SHIELD), R238.1, R301.1, R302.1, R1301.2 (4), R1301.3, U201.1 (GND), U201.3 (GND), U201.12 (GND), U201.14 (GND), U201.22 (WT), U201.23 (DIR), U201.26 (RX2), U201.32 (GND), U201.37 (GND), U201.41 (GND), U201.48 (GND), U201.PAD (GND), U401.2 (GND), U501.2 (GND), U601.6 (GND), U701.2 (GND), U701.3 (GND), U701.5 (GND), U801.6 (GND), U901.A1 (PS), U901.C5 (GND), U901.E1 (GND), U901.E3 (GND), U1001.A1 (VSS), U1101.3 (VSS), U1101.8 (VSS), U1101.9 (VSS), U1201.7 (VSS), U1201.19 (VSS), U1201.31 (VSSA), U1201.43 (VSS), U1301.1 (1~OE), U1301.2 (S1), U1301.8 (GND), U1301.15 (2~OE), U1401.8 (GND), U1402.1 (GND), U1403.1 (GND), Y1201.2, Y1201.4

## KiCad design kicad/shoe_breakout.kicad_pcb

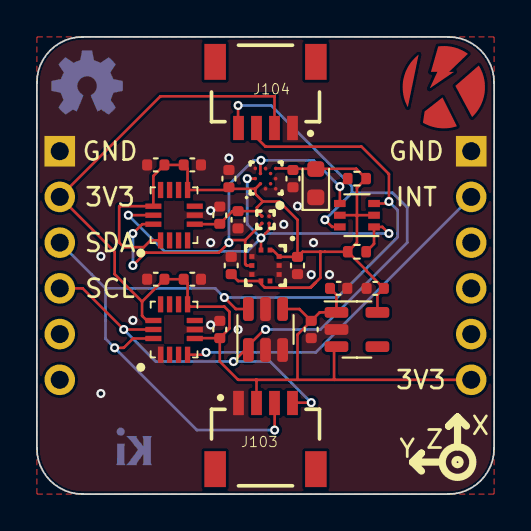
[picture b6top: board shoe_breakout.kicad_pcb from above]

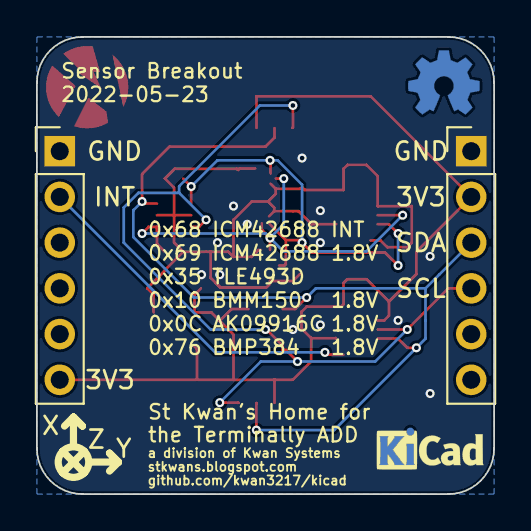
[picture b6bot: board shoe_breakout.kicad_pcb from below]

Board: 2 copper layers, 25.4 x 25.4 mm, 33 parts (4 on the bottom side), 8 nets.

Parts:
C205, C2105: 10nF; C_0402_1005Metric
C206, C2106: 2.2uF; C_0402_1005Metric
C208, C1804, C2108, C2222, C2255, C2411, C2501, C2510: 100nF; C_0402_1005Metric
C1901, C1905: 1uF; C_0402_1005Metric
D1905: RED; LED_0603_1608Metric
G1501: DesignedWithKicad; Symbol_KiCAD-Logo_CopperAndSilkScreenTop_small
G1502: KwanSystems; StKwansSoldermask_0.6
G1503: OSHW; OSHW-Symbol_4x3.6mm_SolderMask
G1505: Axis
J101, J102: Conn_01x06; PinHeader_1x06_P2.54mm_Vertical
J103, J104: 1x04 1mm; JST04_1MM_RA
Q2001: NMOS; SOT-363_SC-70-6
R2001, R2002: 5.1k; R_0402_1005Metric
U201, U2101: ICM-42688; QFN50P300X250X97-14N
U1801: TLE493D-W2B6; SOT-23-6
U1901: TCR2EF 1.8V; SOT-23-5
U2201: BMM150
U2401: AK09918; AK09918C
U2501: BMP384

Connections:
+3V3: C205.1, C206.1, C208.1, C1804.1, C1901.1, J101.2, J102.6, J103.2, J104.2, U201.5 (VDDIO), U201.8 (VDD), U201.12 (~CS), U1801.4 (VDD), U1901.1 (IN), U1901.3 (EN)
/INT: J102.2, U201.4 (INT1)
/SCL: J101.4, J103.4, J104.4, Q2001.6 (D), U201.13 (SCL), U1801.1 (SCL/INT)
/SDA: J101.3, J103.3, J104.3, Q2001.3 (D), U201.14 (SDA), U1801.6 (SDA)
/Sensor Block/Q_1V8: C1905.1, C2105.1, C2106.1, C2108.1, C2222.1, C2255.1, C2411.1, C2501.1, C2510.1, D1905.2 (A), Q2001.2 (G), Q2001.5 (G), R2001.2, R2002.2, U1901.5 (OUT), U2101.1 (AD0), U2101.5 (VDDIO), U2101.8 (VDD), U2101.12 (~CS), U2201.A1 (PS), U2201.B2 (VDDIO), U2201.E5 (VDD), U2401.B1 (VDD), U2501.1 (VDDIO), U2501.6 (CSB), U2501.10 (VDD)
/Sensor Block/SCL_1V8: Q2001.1 (S), R2002.1, U2101.13 (SCL), U2201.A3 (SCK), U2401.A2 (SCL), U2501.2 (SCK)
/Sensor Block/SDA_1V8: Q2001.4 (S), R2001.1, U2101.14 (SDA), U2201.B4 (SDI), U2401.B2 (SDA), U2501.4 (SDI)
GND: C205.2, C206.2, C208.2, C1804.2, C1901.2, C1905.2, C2105.2, C2106.2, C2108.2, C2222.2, C2255.2, C2411.2, C2501.2, C2510.2, D1905.1 (K), J101.1, J102.1, J103.1, J104.1, U201.1 (AD0), U201.6 (GND), U1801.2 (GND), U1801.3 (GND), U1801.5 (GND), U1901.2 (GND), U2101.6 (GND), U2201.A5 (CSB), U2201.C1 (SDO), U2201.C5 (GND), U2201.E1 (GND), U2201.E3 (GND), U2401.A1 (VSS), U2501.3 (VSS), U2501.5 (SDO), U2501.8 (VSS), U2501.9 (VSS)
